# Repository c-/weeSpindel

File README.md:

# weeSpindel

I like the idea of the [iSpindel](https://github.com/universam1/iSpindel),
but I wanted something smaller; ideally, something which I could use in
my glass carboys. This contraint means I need to get it into a tube with
an outside diameter of approximately 25mm.

I've also been trying to get away from Li-ion as a power source and
stick to simple NiMH rechargeables. Using 
[ESP-NOW](https://docs.espressif.com/projects/esp-idf/en/latest/esp32/api-reference/network/esp_now.html)
as a communications
protocol makes a single NiMH cell with a boost converter a realistic
option. However, it turns out that a 25mm tube containing a AA NiMH cell
doesn't have the necessary buoyancy to actually float, much less tilt,
so I've been forced to switch to an AAA cell. In a nod to practicality,
I've also included the option to use a 10440 (AAA-size) Li-ion cell with
a conventional LDO regulator, which seems far more stable at this point.

Stripping out all the bits of the iSpindel that I can't use or don't need,
I'm left with an ESP-12 module, the MPU-6050 module, the power circuitry,
assorted passives, and a single battery cell. Even the DS18B20 temperature
sensor is dropped in favour of the MPU-6050.  Programming the ESP is
handled by either removing it (I mount mine on pin headers) or some sort
of TBD pogo pin jig.

weeSpindel is running a stripped down firmware which transmits
reports using an ESP-NOW broadcast rather than WiFi. ESP-NOW allows
for low-overhead transmission, which reduces the wake-read-send-sleep
cycle to approximately 100-120ms (we only bother with five samples from
the MPU, which honestly might even be excessive).  A ESP-NOW-to-MQTT
(ESP32 with an W5500 ethernet module) gateway makes the sensor results
available in Home Assistant, etc. Configurability is... minimal.

Note that we don't bother with something like a MOSFET to cut power to the
MPU module; between it and the (on my board, at least) Torex XC6204 LDO
it'll use maybe 5uA during sleep. We do remove the LED in the usual
fashion.

# Future

The prototype is done on a PCB mill, and that naturally limits what sort
of component footprints I can comfortably get away with. Future design
using a manufactured PCB opens up a few possibilities.

Lose the MPU-6050 module and put the chip directly on the board.

The failure mode of the HT7733SA boost regulator when the voltage drops
too low (under 1.2v with a AAA NiMH cell) is to go into a approx 200mA
battery draining loop. This is bad. In extreme cases, it'll reverse-charge
the NiMH cell. The fix for this would be to change to a boost regulator
with under-voltage lockout (UVLO). Something like the TPS61097 should do
the trick.

I'd love to get a USB controller onboard for programming. Probably the
CH340E.

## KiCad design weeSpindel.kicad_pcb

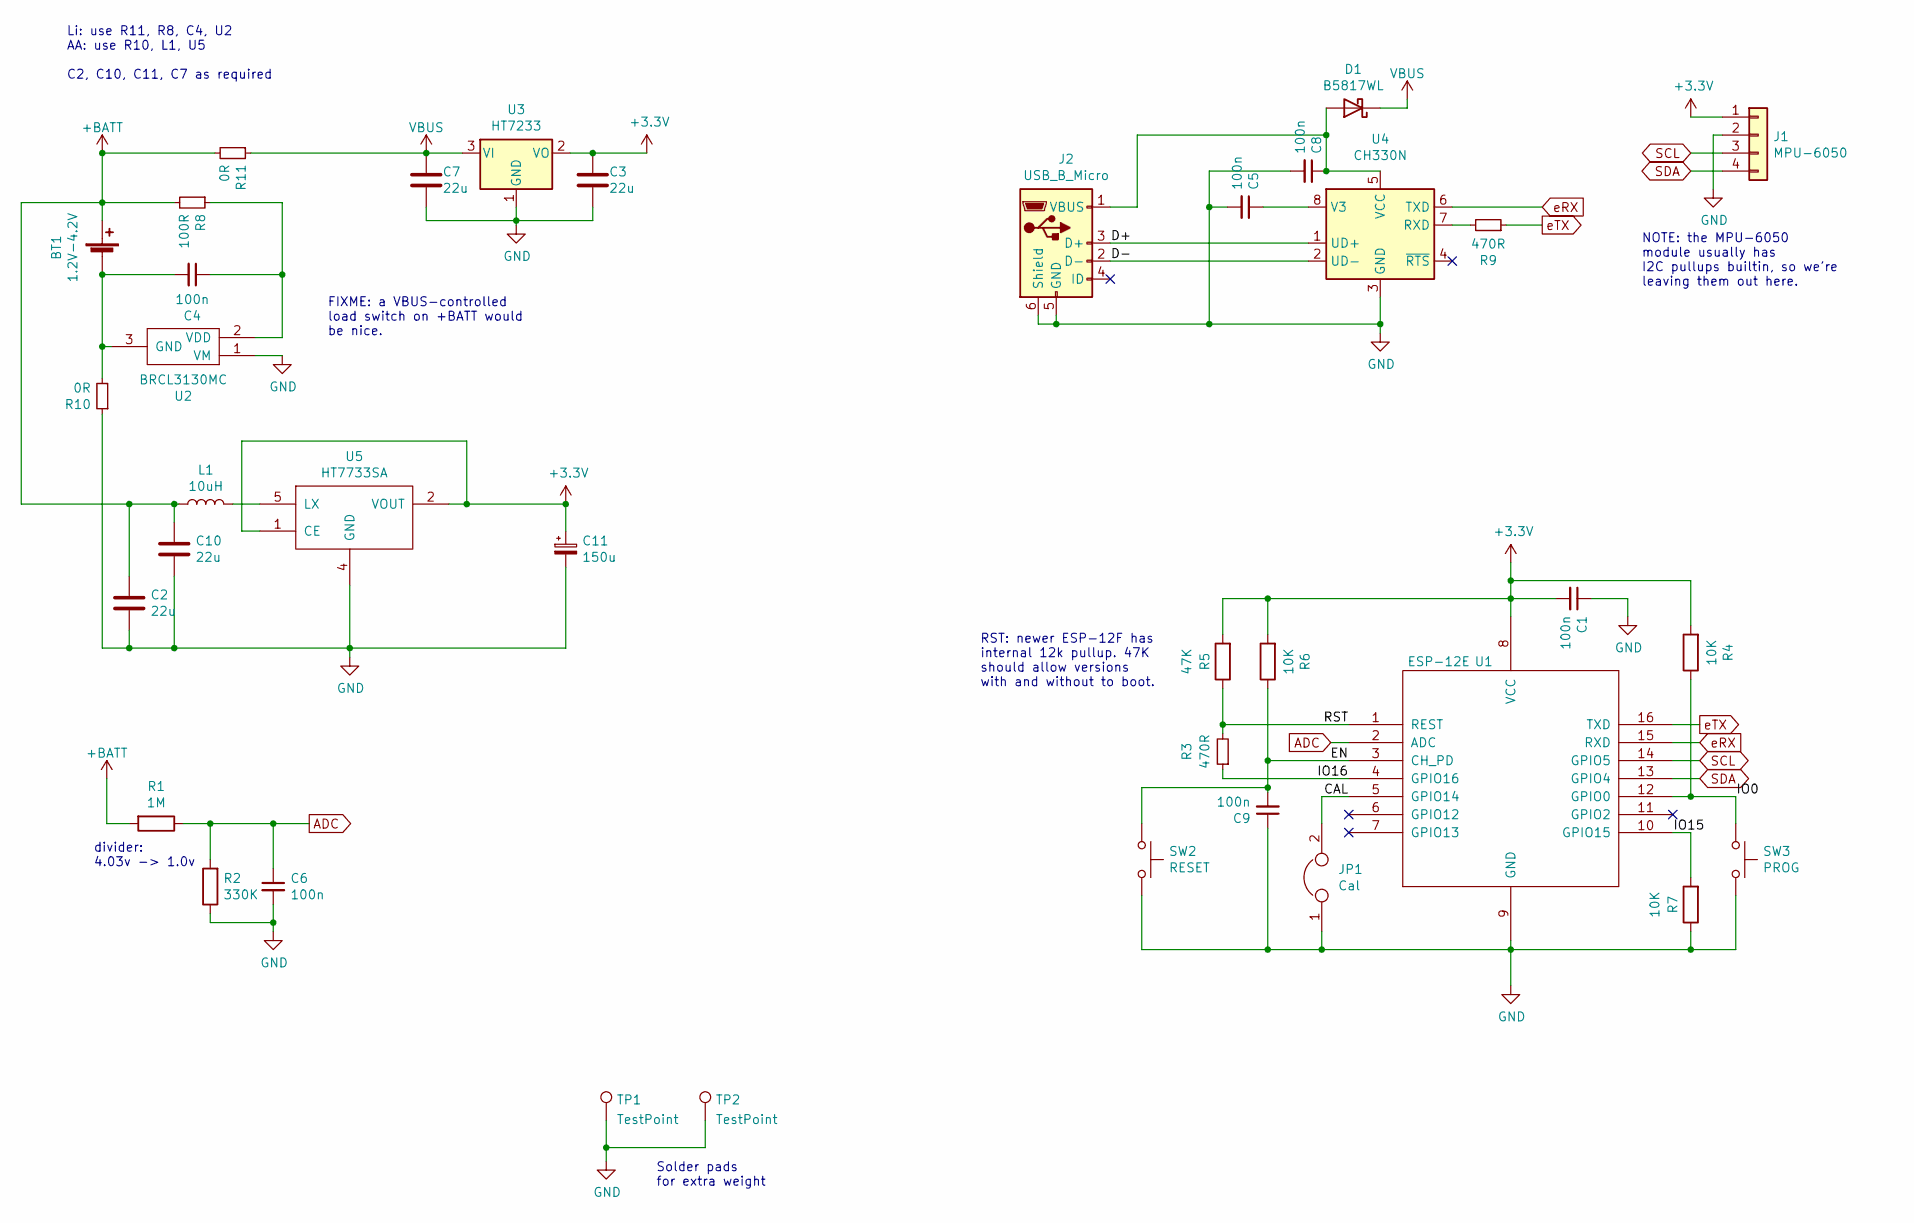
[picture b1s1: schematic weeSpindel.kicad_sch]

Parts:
BT1: 1.2V-4.2V; JST_PH_S2B-PH-K_1x02_P2.00mm_Horizontal
C1, C4, C5, C6, C8, C9: 100n; C_0603_1608Metric_Pad1.08x0.95mm_HandSolder
C2, C3, C7, C10: 22u; C_0805_2012Metric_Pad1.18x1.45mm_HandSolder
C11: 150u; CP_EIA-7343-20_Kemet-V_Pad2.25x2.55mm_HandSolder
D1: B5817WL; D_SOD-123F
J1: MPU-6050; MPU-6050 Breakout I2C
J2: USB_B_Micro; USB Micro-B C10418
JP1: Cal; SW_SPDT_PCM12
L1: 10uH; L_Bourns-SRN4018
R1: 1M; R_0603_1608Metric_Pad0.98x0.95mm_HandSolder
R2: 330K; R_0603_1608Metric_Pad0.98x0.95mm_HandSolder
R3, R9: 470R; R_0603_1608Metric_Pad0.98x0.95mm_HandSolder
R4, R6, R7: 10K; R_0603_1608Metric_Pad0.98x0.95mm_HandSolder
R5: 47K; R_0603_1608Metric_Pad0.98x0.95mm_HandSolder
R8: 100R; R_0603_1608Metric_Pad0.98x0.95mm_HandSolder
R10, R11: 0R; R_0603_1608Metric_Pad0.98x0.95mm_HandSolder
SW2: RESET; SW_SPST_CK_RS282G05A3
SW3: PROG; SW_SPST_CK_RS282G05A3
TP1, TP2: TestPoint; TestPoint_Pad_4.0x4.0mm
U1: ESP-12E; ESP-12Emin
U2: BRCL3130MC; SOT-23_Handsoldering
U3: HT7233; SOT-23_Handsoldering
U4: CH330N; SOIC-8_3.9x4.9mm_P1.27mm
U5: HT7733SA; SOT-23-5_HandSoldering

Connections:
+3V3: C1.2, C3.1, C11.1, J1.1, R4.2, R5.2, R6.2, U1.8 (VCC), U3.2 (VO), U5.1 (CE), U5.2 (VOUT)
+BATT: BT1.1 (+), C2.1, C10.1, L1.1, R1.2, R8.2, R11.2
/CAL: JP1.2, U1.5 (GPIO14)
/D+: J2.3 (D+), U4.1 (UD+)
/D-: J2.2 (D-), U4.2 (UD-)
/EN: C9.2, R6.1, SW2.1, U1.3 (CH_PD)
/IO0: R4.1, SW3.1, U1.12 (GPIO0)
/IO15: R7.2, U1.10 (GPIO15)
/IO16: R3.1, U1.4 (GPIO16)
/RST: R3.2, R5.1, U1.1 (REST)
ADC: C6.1, R1.1, R2.2, U1.2 (ADC)
GND: C1.1, C2.2, C3.2, C5.2, C6.2, C7.2, C8.2, C9.1, C10.2, C11.2, J1.2, J2.5 (GND), J2.6 (Shield), JP1.1, R2.1, R7.1, R10.1, SW2.2, SW3.2, TP1.1, TP2.1, U1.9 (GND), U2.1 (VM), U3.1 (GND), U4.3 (GND), U5.4 (GND)
unnamed: BT1.2 (-), C4.2, R10.2, U2.3 (GND)
unnamed: C4.1, R8.1, U2.2 (VDD)
unnamed: C5.1, U4.8 (V3)
unnamed: C8.1, D1.2 (A), J2.1 (VBUS), U4.5 (VCC)
unnamed: L1.2, U5.5 (LX)
unnamed: R9.2, U4.7 (RXD)
SCL: J1.3, U1.14 (GPIO5)
SDA: J1.4, U1.13 (GPIO4)
VBUS: C7.1, D1.1 (K), R11.1, U3.3 (VI)
eRX: U1.15 (RXD), U4.6 (TXD)
eTX: R9.1, U1.16 (TXD)

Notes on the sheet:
divider: 4.03v -> 1.0v
Li: use R11, R8, C4, U2 AA: use R10, L1, U5 C2, C10, C11, C7 as required
NOTE: the MPU-6050 module usually has I2C pullups builtin, so we're leaving them out here.
FIXME: a VBUS-controlled load switch on +BATT would be nice.
Solder pads for extra weight
RST: newer ESP-12F has internal 12k pullup. 47K should allow versions with and without to boot.

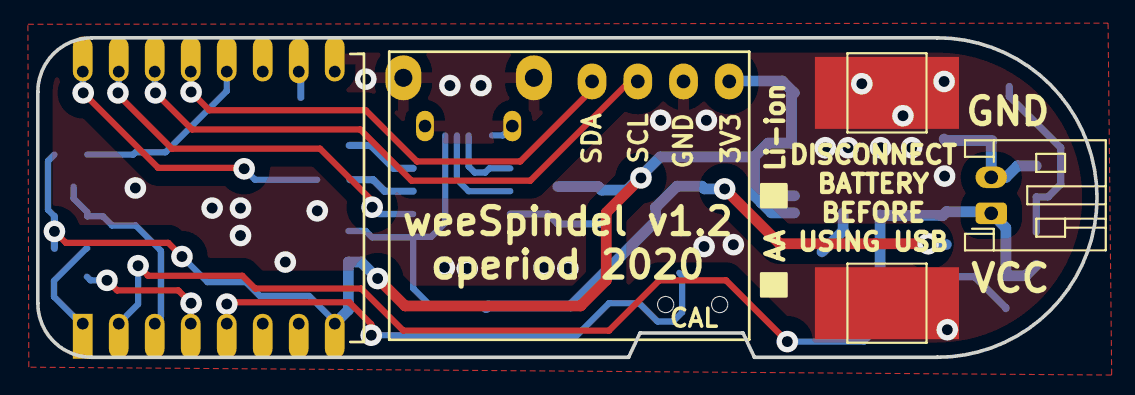
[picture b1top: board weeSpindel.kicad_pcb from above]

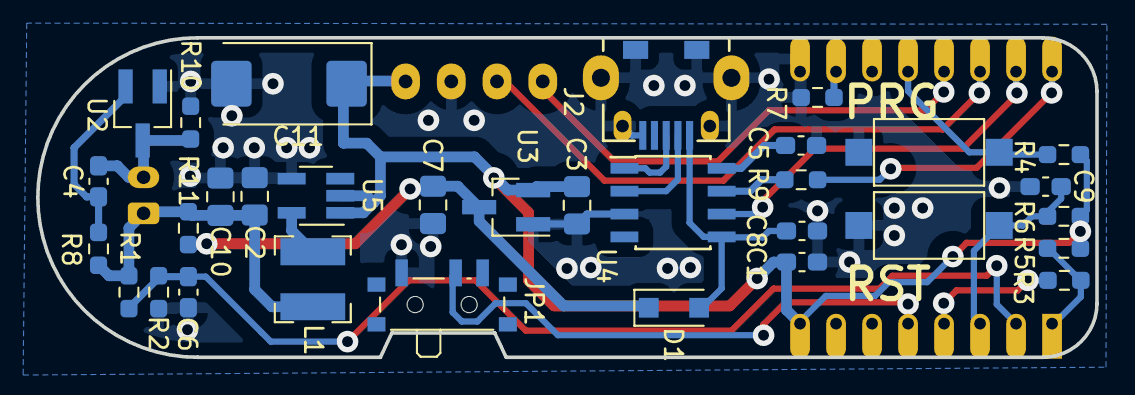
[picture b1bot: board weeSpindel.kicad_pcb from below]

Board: 2 copper layers, 58.8 x 17.8 mm, 37 parts (32 on the bottom side), 23 nets.

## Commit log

2020-04-02 initial import
2020-04-02 another rev
2020-04-02 add a calibrate jumper
2020-04-02 now with integrated battery, power switch.
2020-04-05 that's not something I can solder...
2020-04-05 add some basic firmware
2020-04-05 sync gerbers to PCB
2020-04-05 shut down the sensors before we sleep
2020-04-11 minor update
2020-04-11 lose the DS18
2020-04-11 drop the DS18, switch the MPU to just the four I2C pins, clean up a whole bunch of traces
2020-04-13 looks like we're going to need to switch to an AAA cell if we want this thing to float in such a small container.
2020-04-19 disable RF cal on boot, and rearrange things to waste a bit less power
2020-04-19 a few tweaks
2020-04-19 start writing some sort of documentation
2020-04-19 more power saving
2020-04-19 minor tweaks
2020-04-19 battery cutout was just a touch too narrow.
2020-04-19 battery cutout was a touch too narrow
2020-04-20 using a send callback on a broadcast tells us when it's safe to sleep, reducing our wake time by that entire 100ms.
2020-04-20 the spring on the negative is a bit looser than necessary, allowing us to shave 2mm off our overall length
2020-04-20 more documentation
2020-04-20 tweak the voltage stuff
2020-04-20 trivial
2020-04-20 minor cleanups. Report every 30 minutes. Tighten up timeout/sent logic. Assorted comments.
2020-04-22 comments, tidying, fix for the initial-bad-reading problem. Add the accel samples to the json message.
2020-04-25 a bit of simplifying. We almost certainly don't need that jumper.
2020-04-25 more trace cleanups.
2020-04-25 firmware cleanups, and try removing the I2C pullups.
2020-04-26 add a blank area to write notes, like the ESP ident
2020-04-26 simpler, shorter version that uses lipo battery pack with JST-PH2.0 connectors
2020-06-05 progress on a smaller version using a JST-PH lipo cell off the end
2020-06-05 docs
2020-06-05 add the schematic
2020-06-05 actually, I put those back.
2020-06-05 this is needed to correctly set the wireless channel. Otherwise, we're still broadcasting on channel 1.
2020-06-14 we should have a usable voltage in calibration mode too
2020-06-15 add USB programming
2020-06-19 a bit of tidying up to make it easier to mill and assemble
2020-06-19 more tidying
2021-12-04 add support for both li-ion and NiMH/Alkaline chemistries, plus USB programming. Among other things.
2021-12-04 Kicad 6 update
2021-12-06 some more tidying. ground plane is actually more of a plane now.
